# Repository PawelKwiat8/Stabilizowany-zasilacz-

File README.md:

# Stabilizowany zasilacz - Eagle Autodesk

## Opis projektu
Celem projektu jest zaprojektowanie  i wytworzenie płytki obwodu
drukowanego dla regulowanego stabilizowanego zasilacza laboratoryjnego, a nastepnie pzylutowanie odpowiednich komponentów.

## Schemat elektryczny

## Rozmieszczenie elementów i ścieżek

## Wykonany zasilacz , rozmiar 30x30mm

## Wykaz Elementów

| Symbol   | Nazwa, oznaczenie                        | Ilość |
|----------|------------------------------------------|-------|
| C1, C2, C3, C4 | Kondensator, 100nF, 50V              | 4     |
| C6, C7   | Kondensator, Jamicon, 470uF, 25V        | 2     |
| C5        | Kondensator, Jamicon, 1000uF, 25V      | 1     |
| R1        | Rezystor, R1/4W5%220R                   | 1     |
| R2        | Rezystor, R1/4W5%1k                     | 1     |
| R3        | Potencjometr, RM065 RM-P2, 5x5-502     | 1     |
| IC1       | Stabilizator, ST Microelectronics L7805ACV | 1  |
| IC2       | Stabilizator, ST Microelectronics LM317TT | 1  |
| LED1      | Dioda LED, Yetda Q300HCG1G             | 1     |
| B1        | Mostek prostowniczy, RB157              | 1     |

## Wymagania dotyczące tego obwodu są następujące:
1. Sygnalizacja działania układu: Obwód powinien być wyposażony w diodę
sygnalizacyjną, która wskazuje, czy układ jest włączony i działa
poprawnie.
2. Małe wymiary zewnętrzne: Płytkę obwodu należy zaprojektować tak, aby
jej wymiary były możliwie jak najmniejsze oraz nie utrudniały ręcznego
montażu elementów.
3. Stabilizatory z możliwością montażu radiatora: Stabilizatory zostaną
umieszczone w taki sposób, aby można było dołączyć dodatkowy radiator
w celu efektywnego odprowadzenia ciepła.
4. Brak transformatora: Zasilanie zewnętrzne będzie dostarczane prądem
przemiennym o napięciu do 12V.
5. Zastosowanie rozlanej masy: W projekcie należy uwzględnić
zastosowanie rozlanej masy w celu zwiększenia stabilności i
odprowadzenia ciepła.
6. Układ filtrujący: Zasilacz będzie wyposażony w odpowiedni układ
filtrujący, który pozwoli na uzyskanie czystego napięcia wyjściowego.
7. Jednostronnie wykonana płytką: Płytka obwodu będzie wykonana
metodą grawerowania i trawienia, przy czym będzie to jednostronnie
wykonana płytką drukowaną.
8. Regulowane napięcie wyjściowe: Napięcie wyjściowe będzie można
regulować przy użyciu potencjometru, w zakresie od 2,5V do 12V.
Zadanie polega na zaprojektowaniu i wytworzeniu płytki obwodu
drukowanego, która spełni powyższe wymagania

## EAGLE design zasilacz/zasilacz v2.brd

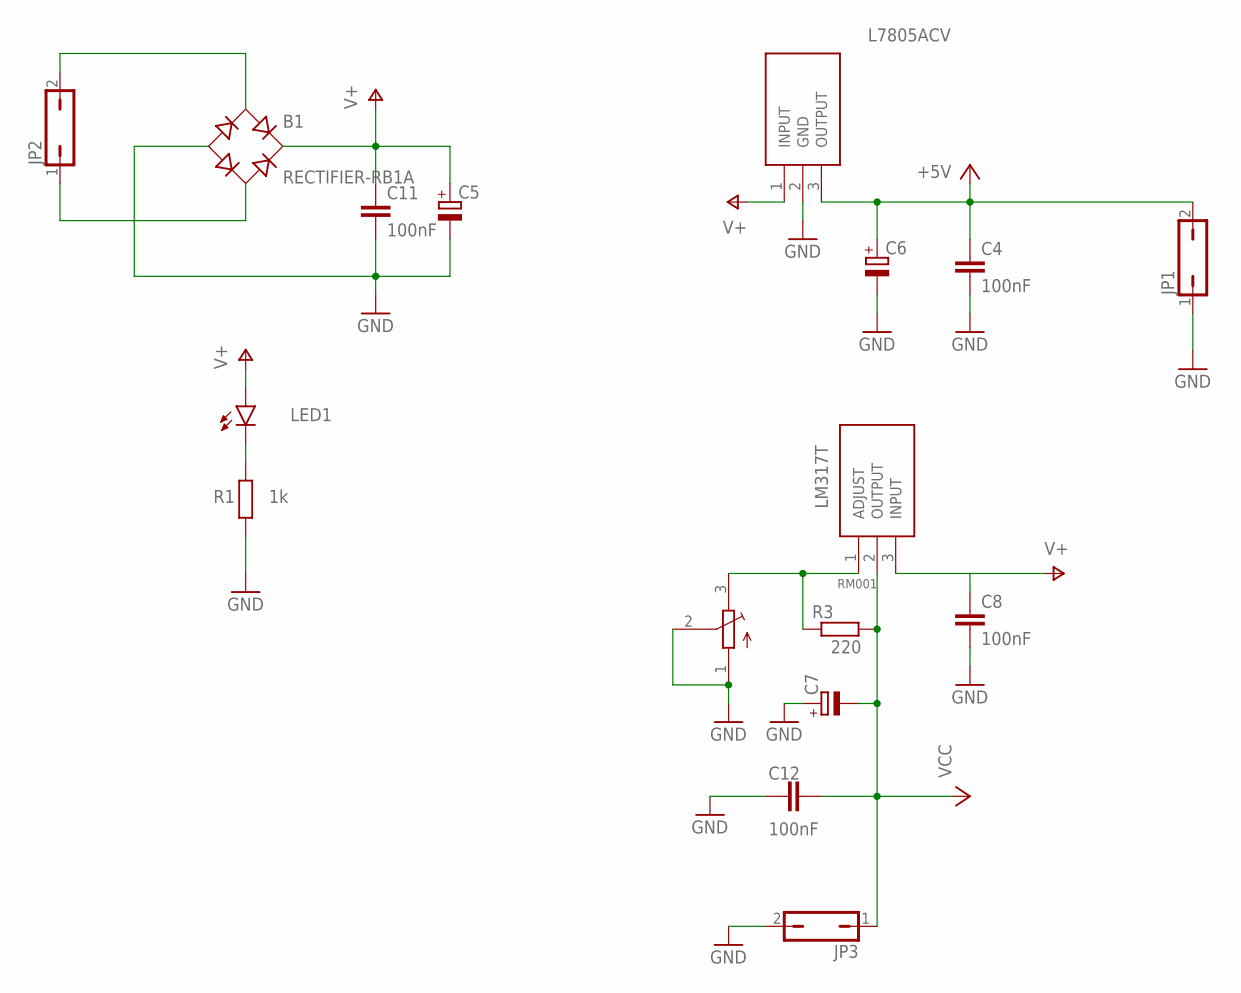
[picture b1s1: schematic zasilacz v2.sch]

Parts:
,1: LM317T; TO255P460X1020X2008-3P
B1: RECTIFIER-RB1A; RB1A
C4, C8, C11, C12: 100nF; C025-024X044
C5, C6, C7: CPOL-EUE5-10.5; E5-10,5
IC1: L7805ACV; TO255P460X1020X2008-3P
JP1, JP2, JP3: JP1Q; JP1
LED1: TLLG4400; LED3MM
R1: 1k; 0204/5
R3: 220; 0204/5
RM001: RM065

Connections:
+5V: C4.1, C6.+, IC1.3 (OUTPUT), JP1.2
GND: B1.-, C4.2, C5.-, C6.-, C7.+, C8.2, C11.2, C12.1, IC1.2 (GND), JP1.1, JP3.2, R1.1, RM001.1, RM001.2
unnamed: LED1.K (C), R1.2
unnamed: ,1.1 (ADJUST), R3.1, RM001.3
unnamed: B1.AC2, JP2.1
unnamed: B1.AC1, JP2.2
V+: ,1.3 (INPUT), B1.+, C5.+, C8.1, C11.1, IC1.1 (INPUT), LED1.A
VCC: ,1.2 (OUTPUT), C7.-, C12.2, JP3.1, R3.2

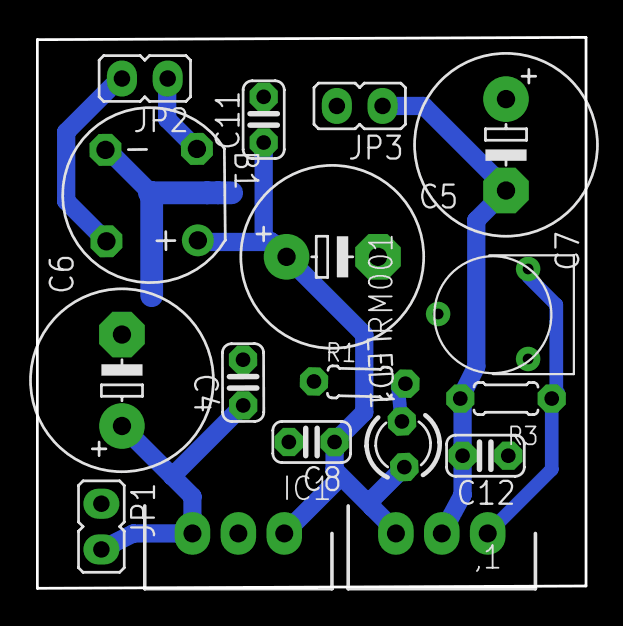
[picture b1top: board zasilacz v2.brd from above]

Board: 2 copper layers, 30.5 x 30.6 mm, 17 parts (0 on the bottom side), 8 nets.

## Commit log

2024-03-23 Rename Paweł Kwiatkowski.png to monochrome.png
2024-03-23 Rename schemat elektryczny .PNG to schemat_elektryczny.PNG
